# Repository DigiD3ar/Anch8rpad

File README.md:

# Anch8rpad
a tiny macropad to control your audio things.

Si quieres un macropad como este baja el zip en la carpeta "gerber" y subelo a un cotizador de pcbs como [JLCPCB](https://jlcpcb.com)
y cotizalo con envio a tu casa.

Para el case hay 2 opciones:
* Case para imprimir hecho por tenochticlack : [link](https://www.thingiverse.com/thing:4680731)
* Case en capas de acrilico por digid3ar : WIP

para armarlo necesitaras lo siguiente : 
* Cautin para soldar
* Estaño
* Flux
* 7 switches
* un encoder
* estabilizador de 2 unidades 
* controlador promicro
* 7 diodos 1N4148
* una perilla.

Y para terminar solo necesitas el archivo firmware en formato hex de para flashearlo con el programa QMK TOOLS en tu pro micro.

Gracias al gran tenochticlack! por el case 3D y su ayuda para la realizacion de este proyecto. siganlo en su [instagram](https://www.instagram.com/tenochticlack)
para mas proyectos pueden seguirme  en mi [instagram](https://www.instagram.com/keeb_lounge)

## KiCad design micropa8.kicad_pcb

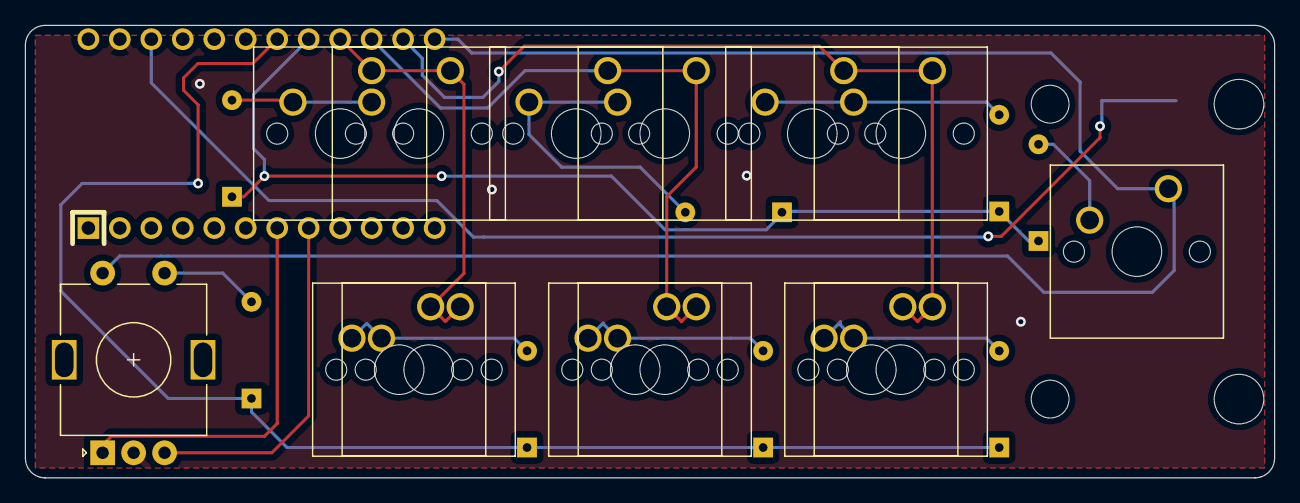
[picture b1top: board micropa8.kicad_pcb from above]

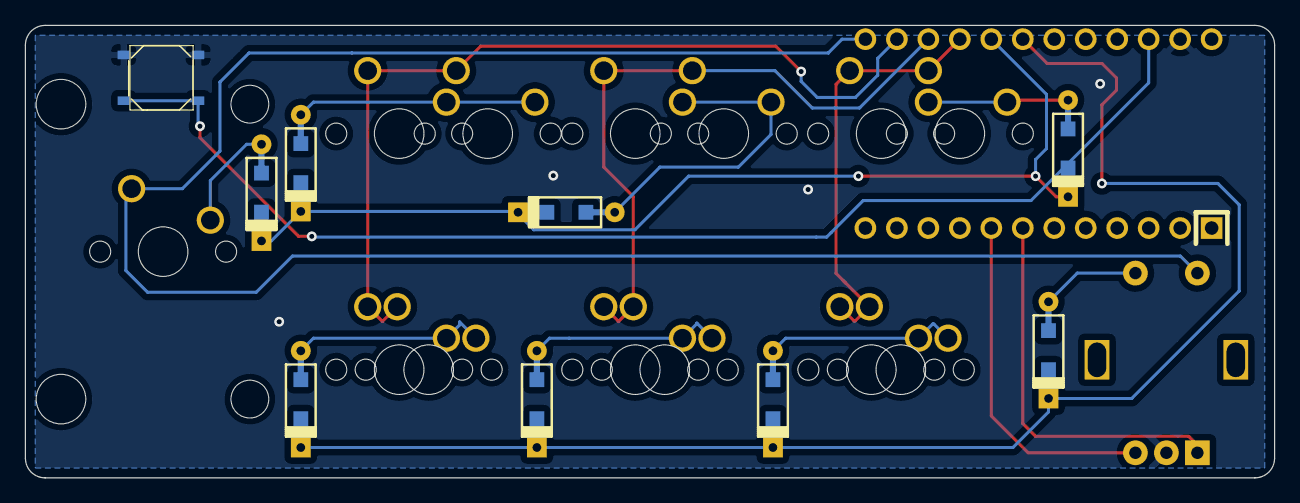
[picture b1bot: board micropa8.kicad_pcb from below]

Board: 2 copper layers, 100.8 x 36.5 mm, 24 parts (9 on the bottom side), 18 nets.

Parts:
D1, D2, D3, D4, D5, D6, D7, D8: D_Small; D_SOD123_axial
MX1, MX2, MX3, MX3#2, MX3#3, MX3#4, MX3#5, MX3#6, MX3#7, MX5, MX6, MX7: MX-NoLED; SW_Cherry_MX_1.00u_PCB
MX4: MX-NoLED; SW_Cherry_MX_ISOEnter_PCB
SW1: SW_Push; SW_TACTILE_SMD
SW3-1: Rotary_Encoder_Switch; RotaryEncoder_Alps_EC11E-Switch_Vertical_H20mm
U1: ProMicro; ArduinoProMicro

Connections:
GND: SW1.1, SW3-1.C, U1.23 (GND)
unnamed: D1.2 (A), MX1.2 (ROW), MX3#3.2 (ROW)
unnamed: D5.2 (A), MX3.2 (ROW), MX5.2 (ROW)
unnamed: D2.2 (A), MX2.2 (ROW), MX3#4.2 (ROW)
unnamed: D6.2 (A), MX6.2 (ROW)
unnamed: D3.2 (A), MX3#6.2 (ROW), MX3#7.2 (ROW)
unnamed: D7.2 (A), MX3#5.2 (ROW), MX7.2 (ROW)
unnamed: D4.2 (A), MX4.2 (ROW)
unnamed: D8.2 (A), SW3-1.S1
unnamed: SW1.2, U1.22 (RST)
col1: MX1.1 (COL), MX3.1 (COL), MX3#3.1 (COL), MX5.1 (COL), U1.16 (B1)
col2: MX2.1 (COL), MX3#2.1 (COL), MX3#4.1 (COL), MX6.1 (COL), U1.15 (B3)
col3: MX3#5.1 (COL), MX3#7.1 (COL), MX7.1 (COL), U1.14 (B2)
col4: MX4.1 (COL), SW3-1.S2, U1.13 (B6)
pinA: SW3-1.A, U1.7 (D4)
pinB: SW3-1.B, U1.8 (C6)
row0: D1.1 (K), D2.1 (K), D3.1 (K), D4.1 (K), U1.17 (F7)
row1: D5.1 (K), D6.1 (K), D7.1 (K), D8.1 (K), U1.18 (F6)

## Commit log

2020-12-09 primera version
2020-12-10 Create README.md
    moar data
2020-12-10 Create LICENSE
